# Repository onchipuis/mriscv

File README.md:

# mriscv

Building a pure RV32I Toolchain
-------------------------------

The default settings in the [riscv-tools](https://github.com/riscv/riscv-tools) build
scripts will build a compiler, assembler and linker that can target any RISC-V ISA,
but the libraries are built for RV32G and RV64G targets. Follow the instructions
below to build a complete toolchain (including libraries) that target a pure RV32I
CPU.

The following commands will build the RISC-V gnu toolchain and libraries for a
pure RV32I target, and install it in `/opt/riscv32i`:

    # Ubuntu packages needed:
    sudo apt-get install autoconf automake autotools-dev curl libmpc-dev libmpfr-dev \
            libgmp-dev gawk build-essential bison flex texinfo gperf libtool patchutils bc

    sudo mkdir /opt/riscv32i
    sudo chown $USER /opt/riscv32i

    git clone https://github.com/riscv/riscv-gnu-toolchain riscv-gnu-toolchain-rv32i
    cd riscv-gnu-toolchain-rv32i
    git checkout 7e48594
    git submodule update --init --recursive

    mkdir build; cd build
    ../configure --with-arch=RV32I --prefix=/opt/riscv32i
    make -j$(nproc)

The Microcontroller
-------------------

The microcontroller is composed by a 32b RISC-V core, a 4KB SRAM, a 10b ADC, a 12b DAC, 8 GPIO, and two SPI interfaces (master and slave). All the modules are conneted using two differente buses: AXI4 and APB.

The directory tree is:

mriscv/mriscv_axi/ADC_interface_AXI     -----> ADC interface with the AXI4 bus

mriscv/mriscv_axi/AXI_SP32B1024         -----> SRAM memory interface

mriscv/mriscv_axi/DAC_interface_AXI     -----> DAC interface with the AXI4 bus

mriscv/mriscv_axi/axi4_interconnect     -----> the AXI4 bus

mriscv/mriscv_axi/impl_axi              -----> the microcontroller

mriscv/mriscv_axi/spi_axi_master        -----> master SPI used for programming

mriscv/mriscv_axi/spi_axi_slave         -----> slave SPI used for data adquisition

Development Board
-----------------

Also, there are a PCB design for the development board, including circuits for sensing analog signals and the capability to use  external clocks. The design is in mriscv/board

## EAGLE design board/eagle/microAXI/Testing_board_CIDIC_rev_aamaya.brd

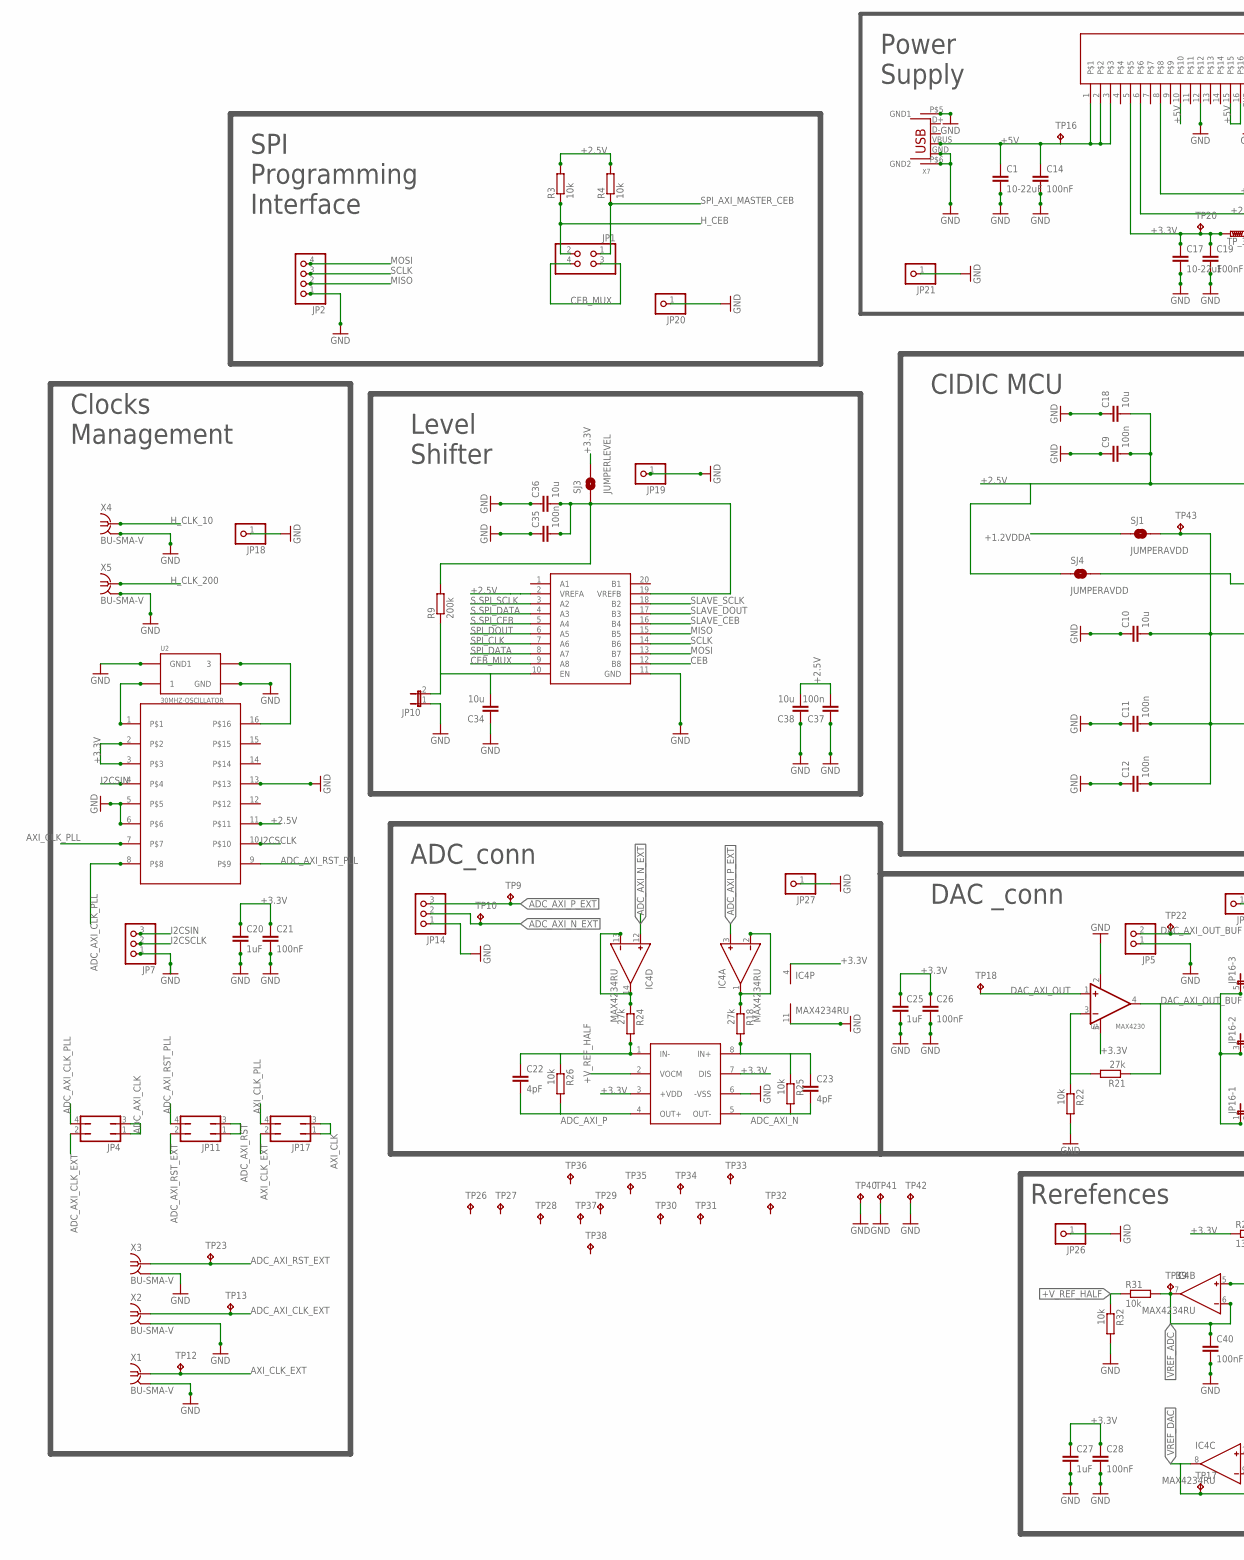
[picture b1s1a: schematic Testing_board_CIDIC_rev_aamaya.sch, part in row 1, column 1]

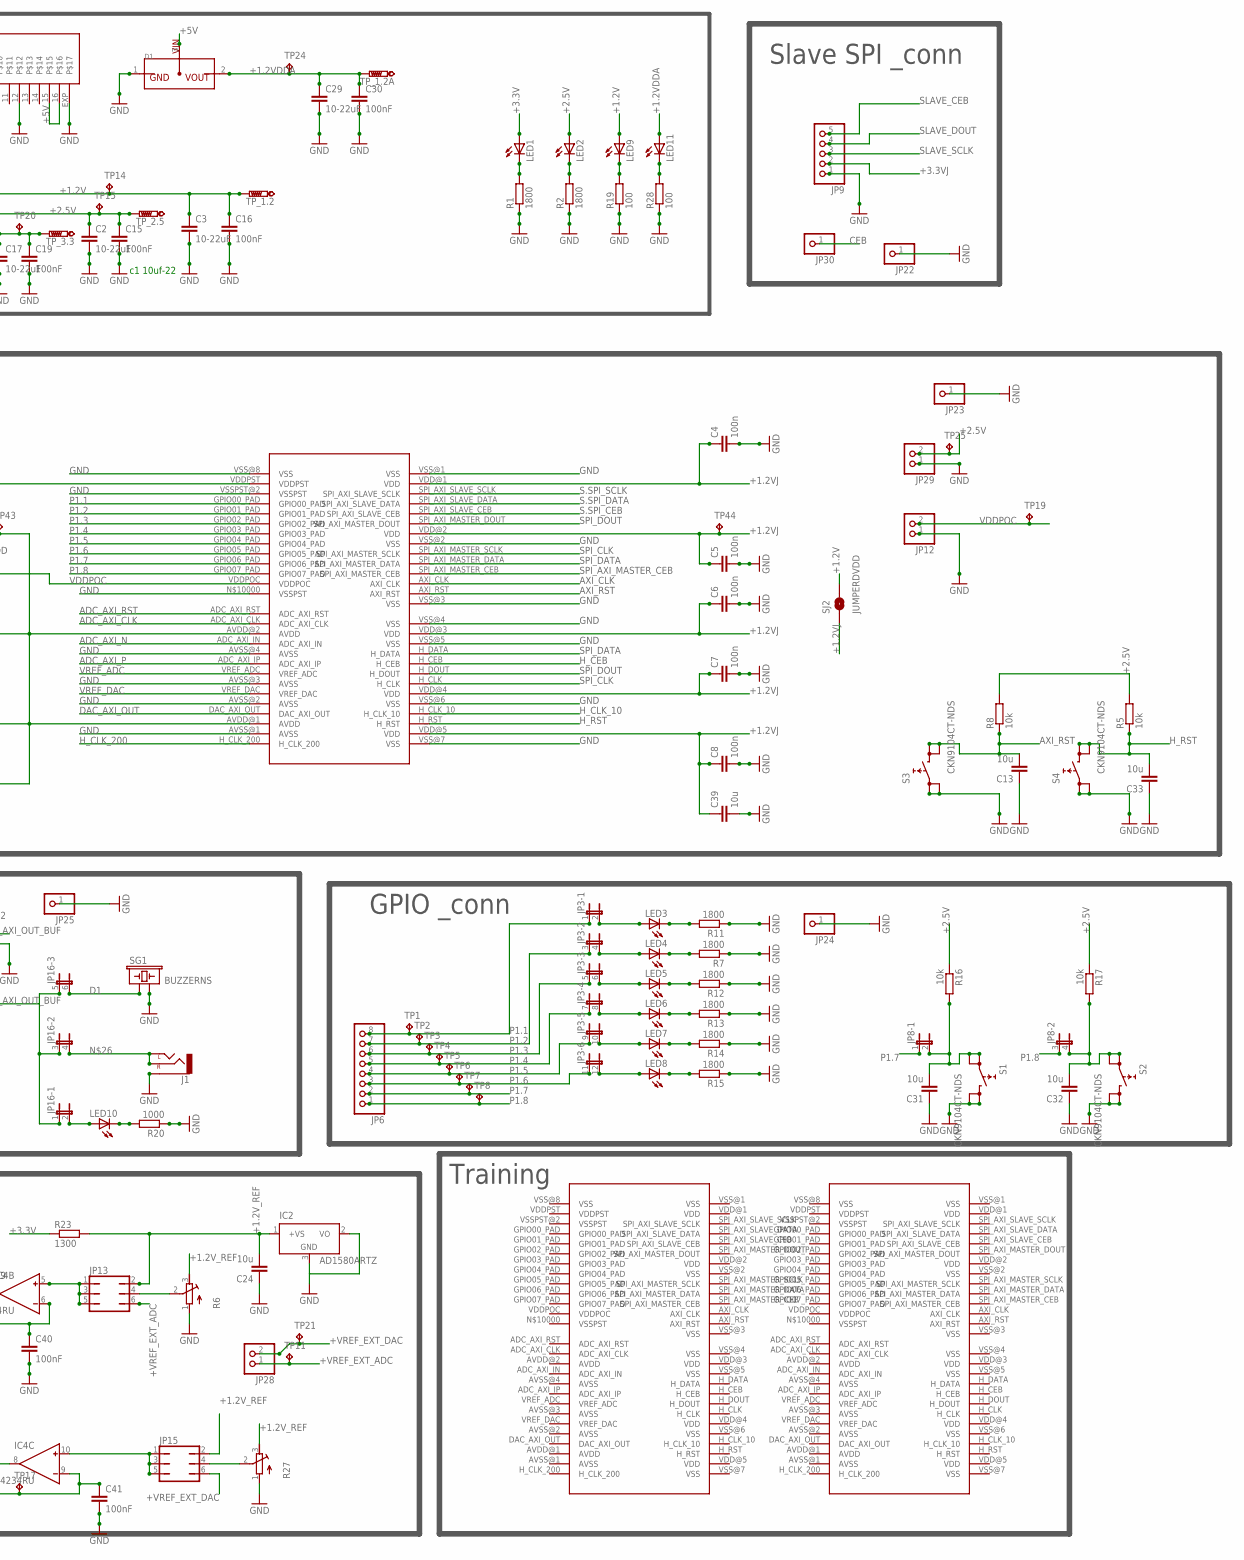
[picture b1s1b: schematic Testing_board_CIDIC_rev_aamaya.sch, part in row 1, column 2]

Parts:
C1, C2, C3, C17, C29: 10-22uF; C0603
C4, C5, C6, C7, C8, C9, C11, C12, C35, C37: 100n; C0603
C10, C13, C18, C24, C31, C32, C33, C34, C36, C38, C39: 10u; C0603
C14, C15, C16, C19, C21, C26, C28, C30, C40, C41: 100nF; C0603
C20, C25, C27: 1uF; C0603
C22, C23: 4pF; C0603
D1: MCP1700T-1202E/TTCT-ND; SOT-23
GND: ADP322; LFCSP_LQ-16
IC2: AD1580ARTZ; SOT23
IC4: MAX4234RU; TSSOP14
J1: AUDIO-JACK_DIGIKEYSMD; STEREOJACK2.5MM_SMD
JP1: PINHD-2X2; 2X02
JP2: PINHD-1X4; 1X04
JP3: JP6QE; JP6Q
JP4, JP11, JP17: JP2Q
JP5, JP12, JP28, JP29: PINHD-1X2; 1X02
JP6: PINHD-1X8; 1X08
JP7, JP14: PINHD-1X3; 1X03
JP8: JP2QE; JP2Q
JP9: PINHD-1X5; 1X05
JP10: JP1E; JP1
JP13, JP15: JP3Q
JP16: JP3QE; JP3Q
JP18, JP19, JP20, JP21, JP22, JP23, JP24, JP25, JP26, JP27, JP30: PINHD-1X1; 1X01
LED1, LED2, LED9, LED10, LED11: LEDSML0805; SML0805
LED3, LED4, LED5, LED6, LED7, LED8: LEDCHIPLED_0805; CHIPLED_0805
R1, R2, R7, R11, R12, R13, R14, R15: 1800; R0603
R3, R4, R5, R8, R16, R17, R22, R25, R26, R31, R32: 10k; R0603
R6, R27: R-TRIMM4G/J; RTRIM4G/J
R9: 200k; R0603
R18, R21, R24: 27k; R0603
R19, R28: 100; R0603
R20: 1000; R0603
R23: 1300; R0603
S1, S2, S3, S4: CKN9104CT-NDS; SKHMPXE010
SG1: BUZZERNS; BUZZER-12MM-NS
SJ1, SJ4: JUMPERAVDD; SJ_ROUND
SJ2: JUMPERDVDD; SJ_ROUND
SJ3: JUMPERLEVEL; SJ_ROUND
TP1, TP2, TP3, TP4, TP5, TP6, TP7, TP8, TP9, TP10, TP11, TP12, TP13, TP14, TP15, TP16, TP17, TP18, TP19, TP20, TP21, TP22, TP23, TP24, TP25, TP39, TP40, TP41, TP42, TP43, TP44: TPTP20R; TP20R
TP26, TP27, TP28, TP29, TP30, TP31, TP32, TP33, TP34, TP35, TP36, TP37, TP38: TPTP08R; TP08R
TP_1.2, TP_1.2A, TP_2.5, TP_3.3: PTR1B1,27; B1,27
U1: MAX4230; SC-70-5
U2: 30MHZ-OSCILLATOR; 5X3.2
U$1, U$6, U$7: CIDIC_AXI_UC_TEST_DIE
U$3: LEVEL_SHIFTER_8; TSSOP20
U$4: CY22150KFZXC; TSSOP16
U$5: ADA4940; SO8
X1, X2, X3, X4, X5: BU-SMA-V
X7: USB-A-H

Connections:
+1.2V: C3.1, C16.1, GND.8, LED9.A, SJ2.2, TP14.TP, TP_1.2.TP
+1.2VDDA: C29.1, C30.1, D1.2 (VOUT), LED11.A, SJ1.1, TP24.TP, TP_1.2A.TP
+1.2VJ: C4.1, C5.1, C6.1, C7.1, C8.1, C39.1, SJ2.1, TP44.TP, U$1.VDD@1 (VDD), U$1.VDD@2 (VDD), U$1.VDD@3 (VDD), U$1.VDD@4 (VDD), U$1.VDD@5 (VDD)
+1.2V_REF: C24.2, IC2.1 (+VS), JP13.2, JP15.2, R6.3 (E), R23.2, R27.3 (E)
+2.5V: C2.1, C9.2, C15.1, C18.2, C37.2, C38.2, GND.6, JP29.2, LED2.A, R3.2, R4.2, R5.2, R8.2, R16.1, R17.1, SJ4.1, TP15.TP, TP25.TP, TP_2.5.TP, U$1.VDDPST, U$3.2 (VREFA), U$4.11
+3.3V: C17.1, C19.1, C20.1, C21.1, C25.1, C26.1, C27.1, C28.1, GND.5, IC4.4 (V+), LED1.A, R23.1, SJ3.2, TP20.TP, TP_3.3.TP, U1.5 (V+), U$4.2, U$4.3, U$5.3 (+VDD), U$5.7 (DIS)
+3.3VJ: C35.2, C36.2, JP9.2, R9.2, SJ3.1, U$3.19 (VREFB)
+5V: C1.1, C14.1, D1.3 (VIN), GND.1, GND.2, GND.3, GND.10, GND.15, GND.16, TP16.TP, X7.VBUS
+VREF_EXT_ADC: JP13.6, JP28.1, TP11.TP
+VREF_EXT_DAC: JP15.6, JP28.2, TP21.TP
+V_REF_HALF: R31.1, R32.1, U$5.2 (VOCM)
ADC_AXI_CLK: JP4.1, JP4.3, U$1.ADC_AXI_CLK
ADC_AXI_CLK_EXT: JP4.2, TP13.TP, X2.1
ADC_AXI_CLK_PLL: JP4.4, U$4.8
ADC_AXI_N: C23.2, R25.2, U$1.ADC_AXI_IN, U$5.5 (OUT-)
ADC_AXI_N_EXT: IC4.12 (IN+), JP14.2, TP10.TP
ADC_AXI_P: C22.2, R26.2, U$1.ADC_AXI_IP, U$5.4 (OUT+)
ADC_AXI_P_EXT: IC4.3 (IN+), JP14.3, TP9.TP
ADC_AXI_RST: JP11.1, JP11.3, U$1.ADC_AXI_RST
ADC_AXI_RST_EXT: JP11.2, TP23.TP, X3.1
ADC_AXI_RST_PLL: JP11.4, U$4.9
AXI_CLK: JP17.1, JP17.3, U$1.AXI_CLK
AXI_CLK_EXT: JP17.2, TP12.TP, X1.1
AXI_CLK_PLL: JP17.4, U$4.7
AXI_RST: C13.2, R8.1, S3.3 (2.1), S3.4 (2.2), U$1.AXI_RST
CEB: JP30.1, U$3.12 (B8)
CEB_MUX: JP1.3, JP1.4, U$3.9 (A8)
D1: JP16.6 (2), SG1.+ (1)
D3: JP16.2, LED10.A
DAC_AXI_OUT: TP18.TP, U1.1 (IN+), U$1.DAC_AXI_OUT
DAC_AXI_OUT_BUF: JP5.2, JP16.1, JP16.3 (1), JP16.5 (1), R21.1, TP22.TP, U1.4 (OUT)
GND: C1.2, C2.2, C3.2, C4.2, C5.2, C6.2, C7.2, C8.2, C9.1, C10.1, C11.1, C12.1, C13.1, C14.2, C15.2, C16.2, C17.2, C18.1, C19.2, C20.2, C21.2, C24.1, C25.2, C26.2, C27.2, C28.2, C29.2, C30.2, C31.1, C32.1, C33.1, C34.1, C35.1, C36.1, C37.1, C38.1, C39.2, C40.2, C41.2, D1.1 (GND), GND.12, GND.EXP, IC2.2 (VO), IC2.3 (GND), IC4.11 (V-), J1.1 (SLEEVE), JP2.1, JP5.1, JP7.1, JP9.1, JP10.1, JP12.1, JP14.1, JP18.1, JP19.1, JP20.1, JP21.1, JP22.1, JP23.1, JP24.1, JP25.1, JP26.1, JP27.1, JP29.1, R1.1, R2.1, R6.1 (A), R7.1, R11.1, R12.1, R13.1, R14.1, R15.1, R19.1, R20.1, R22.2, R27.1 (A), R28.1, R32.2, S1.3 (2.1), S1.4 (2.2), S2.3 (2.1), S2.4 (2.2), S3.1 (1.1), S3.2 (1.2), S4.1 (1.1), S4.2 (1.2), SG1.- (2), TP40.TP, TP41.TP, TP42.TP, U1.2 (V-), U2.2 (GND), U2.4 (GND1), U$1.AVSS@1 (AVSS), U$1.AVSS@2 (AVSS), U$1.AVSS@3 (AVSS), U$1.AVSS@4 (AVSS), U$1.N$10000 (VSSPST), U$1.VSS@1 (VSS), U$1.VSS@2 (VSS), U$1.VSS@3 (VSS), U$1.VSS@4 (VSS), U$1.VSS@5 (VSS), U$1.VSS@6 (VSS), U$1.VSS@7 (VSS), U$1.VSS@8 (VSS), U$1.VSSPST@2 (VSSPST), U$3.11 (GND), U$4.5, U$4.6, U$4.13, U$5.6 (-VSS), X1.2, X1.3 (2), X1.4 (2), X1.5 (2), X2.2, X2.3 (2), X2.4 (2), X2.5 (2), X3.2, X3.3 (2), X3.4 (2), X3.5 (2), X4.2, X4.3 (2), X4.4 (2), X4.5 (2), X5.2, X5.3 (2), X5.4 (2), X5.5 (2), X7.GND, X7.P$5 (GND1), X7.P$6 (GND2)
H_CEB: JP1.2, R3.1, U$1.H_CEB
H_CLK_10: U$1.H_CLK_10, X4.1
H_CLK_200: U$1.H_CLK_200, X5.1
H_RST: C33.2, R5.1, S4.3 (2.1), S4.4 (2.2), U$1.H_RST
I2CSCLK: JP7.2, U$4.10
I2CSIN: JP7.3, U$4.4
JV12A: C10.2, C11.2, C12.2, SJ1.2, TP43.TP, U$1.AVDD@1 (AVDD), U$1.AVDD@2 (AVDD)
MISO: JP2.2, U$3.15 (B5)
MOSI: JP2.4, U$3.13 (B7)
unnamed: U2.1, U$4.1
unnamed: LED1.C, R1.2
unnamed: LED2.C, R2.2
unnamed: C22.1, R24.2, R26.1, U$5.1 (IN-)
unnamed: LED9.C, R19.2
unnamed: C31.2, JP8.2, R16.2, S1.1 (1.1), S1.2 (1.2)
unnamed: C32.2, JP8.4 (2), R17.2, S2.1 (1.1), S2.2 (1.2)
unnamed: C23.1, R18.2, R25.1, U$5.8 (IN+)
unnamed: U2.3, U$4.16
unnamed: JP13.4, R6.2 (S)
unnamed: LED11.C, R28.2
unnamed: IC4.13 (IN-), IC4.14 (OUT), R24.1
unnamed: LED4.C, R7.2
unnamed: JP3.4 (2), LED4.A
unnamed: JP3.6 (2), LED5.A
unnamed: JP3.8 (2), LED6.A
unnamed: JP3.10 (2), LED7.A
unnamed: JP3.2, LED3.A
unnamed: LED3.C, R11.2
unnamed: JP3.12 (2), LED8.A
unnamed: LED5.C, R12.2
unnamed: LED6.C, R13.2
unnamed: LED7.C, R14.2
unnamed: LED8.C, R15.2
unnamed: J1.2 (LEFT), J1.3 (RIGHT), JP16.4 (2)
unnamed: IC4.1 (OUT), IC4.2 (IN-), R18.1
unnamed: R21.2, R22.1, U1.3 (IN-)
unnamed: LED10.C, R20.2
unnamed: IC4.10 (IN+), JP15.1, JP15.3, JP15.5
unnamed: IC4.5 (IN+), JP13.1, JP13.3, JP13.5
unnamed: JP15.4, R27.2 (S)
unnamed: C34.2, JP10.2, R9.1, U$3.10 (EN)
P1.1: JP3.1, JP6.8, TP1.TP, U$1.GPIO00_PAD
P1.2: JP3.3 (1), JP6.7, TP2.TP, U$1.GPIO01_PAD
P1.3: JP3.5 (1), JP6.6, TP3.TP, U$1.GPIO02_PAD
P1.4: JP3.7 (1), JP6.5, TP4.TP, U$1.GPIO03_PAD
P1.5: JP3.9 (1), JP6.4, TP5.TP, U$1.GPIO04_PAD
P1.6: JP3.11 (1), JP6.3, TP6.TP, U$1.GPIO05_PAD
P1.7: JP6.2, JP8.1, TP7.TP, U$1.GPIO06_PAD
P1.8: JP6.1, JP8.3 (1), TP8.TP, U$1.GPIO07_PAD
S.SPI_CEB: U$1.SPI_AXI_SLAVE_CEB, U$3.5 (A4)
S.SPI_DATA: U$1.SPI_AXI_SLAVE_DATA, U$3.4 (A3)
S.SPI_SCLK: U$1.SPI_AXI_SLAVE_SCLK, U$3.3 (A2)
SCLK: JP2.3, U$3.14 (B6)
SLAVE_CEB: JP9.5, U$3.16 (B4)
SLAVE_DOUT: JP9.4, U$3.17 (B3)
SLAVE_SCLK: JP9.3, U$3.18 (B2)
SPI_AXI_MASTER_CEB: JP1.1, R4.1, U$1.SPI_AXI_MASTER_CEB
SPI_CLK: U$1.H_CLK, U$1.SPI_AXI_MASTER_SCLK, U$3.7 (A6)
SPI_DATA: U$1.H_DATA, U$1.SPI_AXI_MASTER_DATA, U$3.8 (A7)
SPI_DOUT: U$1.H_DOUT, U$1.SPI_AXI_MASTER_DOUT, U$3.6 (A5)
VDDPOC: JP12.2, SJ4.2, TP19.TP, U$1.VDDPOC
VREF_ADC: C40.1, IC4.6 (IN-), IC4.7 (OUT), R31.2, TP39.TP, U$1.VREF_ADC
VREF_DAC: C41.1, IC4.8 (OUT), IC4.9 (IN-), TP17.TP, U$1.VREF_DAC

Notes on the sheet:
Power Supply
SPI Programming Interface
Clocks Management
ADC_conn
DAC _conn
GPIO _conn
Slave SPI _conn
Level Shifter
CIDIC MCU
Rerefences
c1 10uf-22
Training

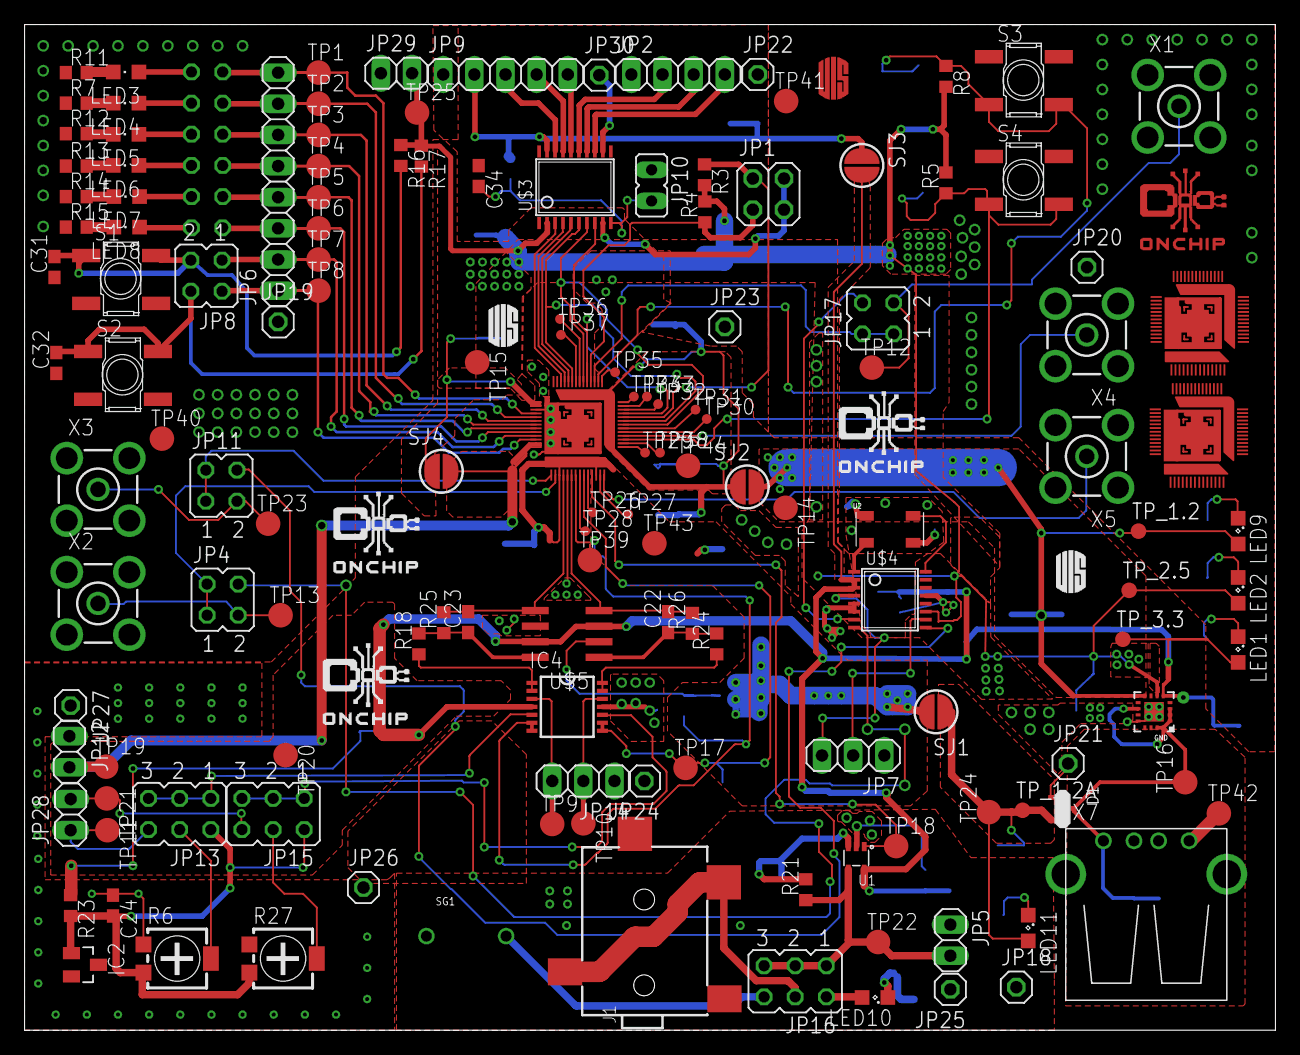
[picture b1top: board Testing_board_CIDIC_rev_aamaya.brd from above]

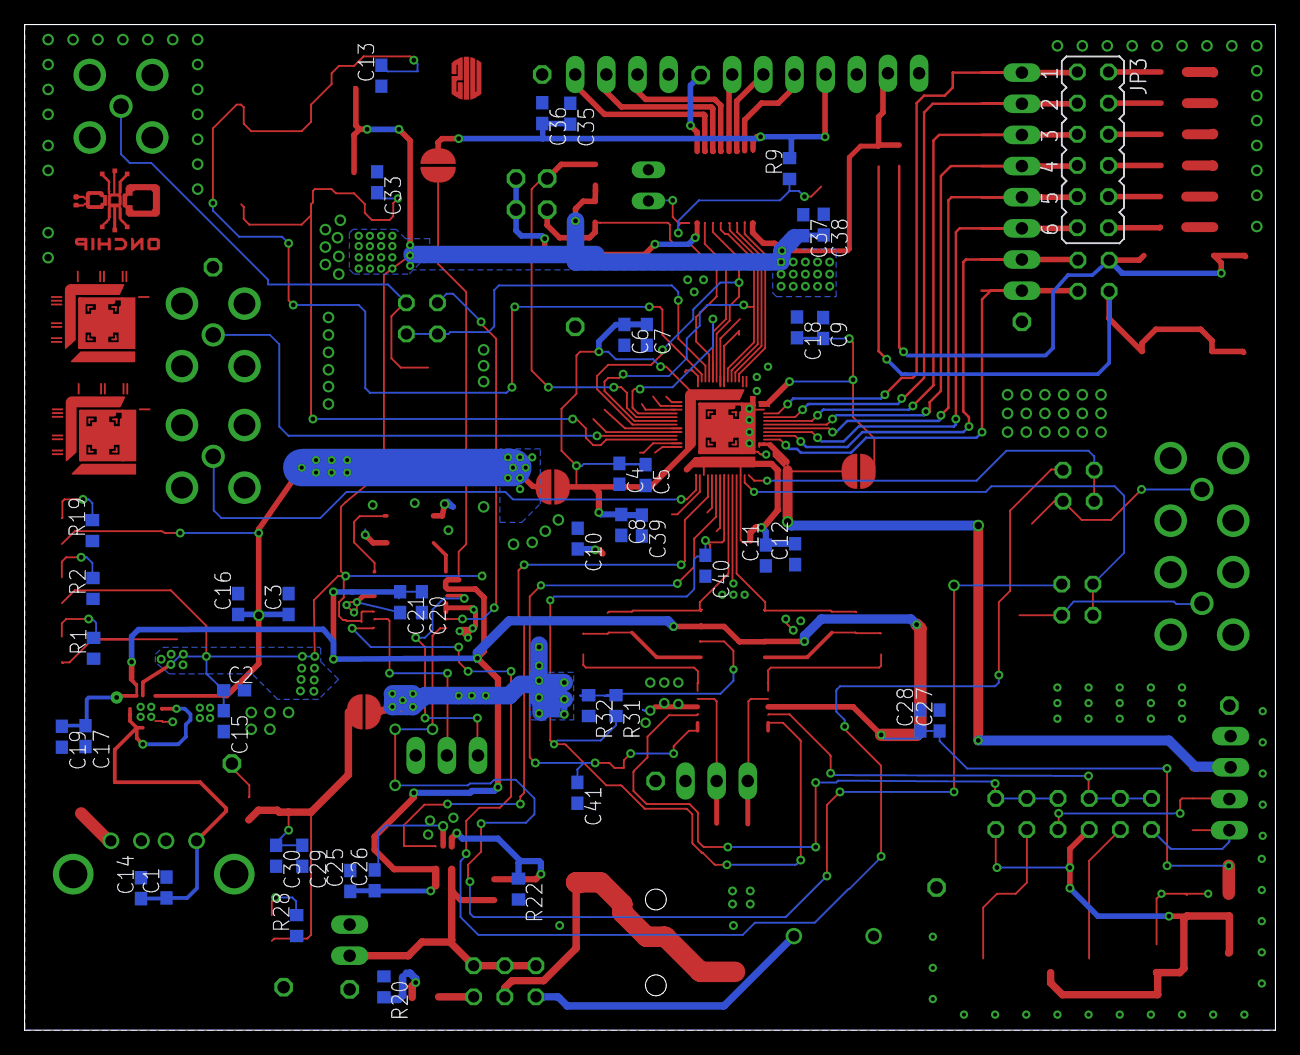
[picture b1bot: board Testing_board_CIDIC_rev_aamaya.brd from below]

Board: 2 copper layers, 102.0 x 82.0 mm, 187 parts (45 on the bottom side), 95 nets.

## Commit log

2016-09-29 workaround
2016-10-01 Toolchain generation
2016-10-02 Add board things
2016-11-21 Create LICENSE
2016-11-28 Create .gitignore
    Currently just EagleCAD files.
2016-12-27 Add files via upload
    A Fully-Synthesized TRNG with Lightweight Cellular-Automata Based Post-Processing Stage in 130nm CMOS
2017-03-13 Add mriscvcore
2017-03-13 Moved submodule mriscvcore to PowerAnalysis
2017-03-14 Added GPIO and Util
2017-04-11 Update from private repository
2017-04-11 Update mriscvcore
2017-04-12 Workaround for verilog sim in mriscv_vivado
2017-04-12 Workaround for firmware utilization
2017-04-19 Limit fix
2017-04-19 Fix limiter
2017-07-16 Updating mriscvcore
2017-07-17 Updating
2017-07-27 Info update
2018-02-28 Add priority encoder missing

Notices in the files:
parts and their libraries:
SparkFun-Electromechanical: Licensing: CC v3.0 Share-Alike You are welcome to use this library for commercial purposes.
SparkFun-Retired: Licensing:Creative Commons ShareAlike 4.0 International - https://creativecommons.org/licenses/by-sa/4.0
